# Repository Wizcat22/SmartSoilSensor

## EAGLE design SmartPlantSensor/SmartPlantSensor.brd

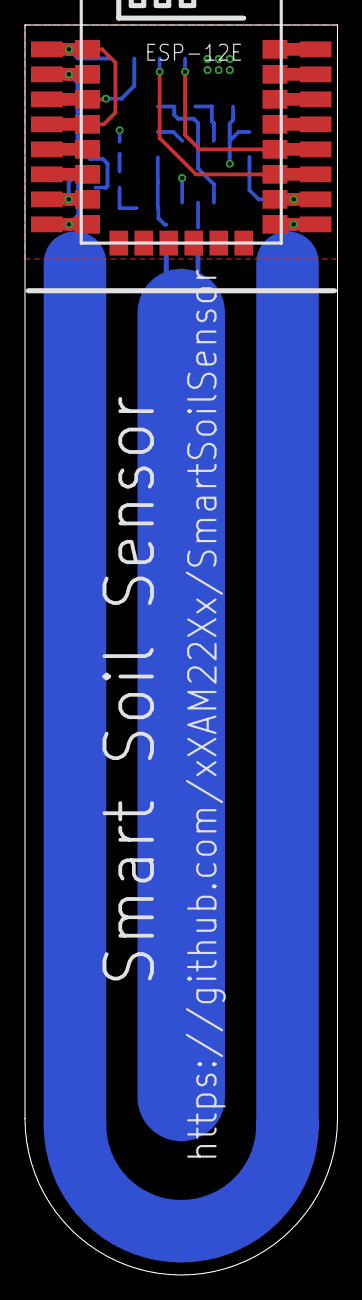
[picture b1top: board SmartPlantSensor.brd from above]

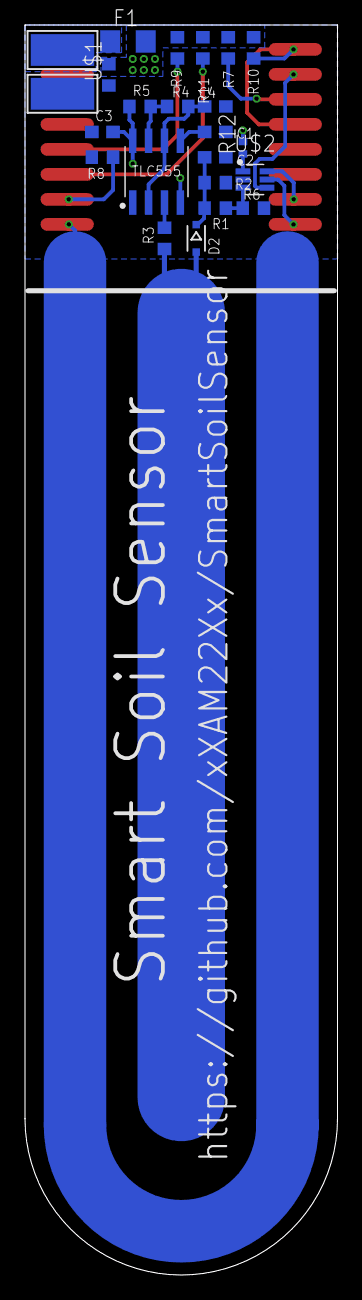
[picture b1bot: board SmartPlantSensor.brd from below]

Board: 2 copper layers, 25.0 x 100.0 mm, 40 parts (23 on the bottom side), 24 nets.

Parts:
C1: 10nF; C0603
C2: 1uF; C0603
C3: 100nF; C0603
C4: 470pF; C0603
D2: 1N4148WS; SOD323-R
ESP-12E: ESP-12E
F1: FUSE; R1206
PAD1, PAD3: WIREPADSMD5-2,5; 5-2,5
PAD5, PAD6, PAD7, PAD8, PAD9, PAD10, PAD11, PAD12, PAD13, PAD14, PAD15, PAD16, PAD17, PAD18, PAD19, PAD20: SMD1,27-2,54
R1: 220k; R0603
R2: 1M; R0603
R3, R7, R8, R9, R10, R11: 10k; R0603
R4: 1k6; R0603
R5: 330; R0603
R6: 100k; R0603
R12: 0; R0402
TLC555: TLC555CD; SOIC8
U$1: TVS_BI_DIODE; R0603
U$2: PI5A3157; SOT65P210X110-6

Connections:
+3V3: C3.2, ESP-12E.8, F1.2, PAD12.1, R5.1, R7.2, R9.2, R10.2, R11.2, R12.2, TLC555.4, TLC555.8, U$1.2, U$2.5
ADC: ESP-12E.2, PAD6.1, U$2.4
DISCH: R4.1, R5.2, TLC555.7
EN: ESP-12E.3, PAD7.1, R7.1
GND: C1.1, C2.2, C3.1, C4.1, ESP-12E.15, PAD3.1, PAD20.1, R2.1, R6.1, R8.1, TLC555.1, U$1.1, U$2.2
IO0: ESP-12E.18, PAD17.1, R9.1
IO2: ESP-12E.17, PAD18.1, R11.1
IO4: ESP-12E.19, PAD16.1
IO5: ESP-12E.20, PAD15.1
IO12: ESP-12E.6, PAD10.1
IO13: ESP-12E.7, PAD11.1, U$2.6
IO14: ESP-12E.5, PAD9.1
IO15: ESP-12E.16, PAD19.1, R8.2
unnamed: C1.2, TLC555.5
unnamed: R12.1, U$2.1
OUT: R3.1, TLC555.3
RST: ESP-12E.1, ESP-12E.4, PAD5.1, PAD8.1, R10.1
RXD: ESP-12E.21, PAD14.1
SADC: R1.1, R6.2, U$2.3
SENSOR: D2.A, R3.2
SENSOR_OUT: C2.1, D2.C, R1.2, R2.2
T: C4.2, R4.2, TLC555.2, TLC555.6
TXD: ESP-12E.22, PAD13.1
VCC: F1.1, PAD1.1

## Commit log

2018-08-21 Create LICENSE
2018-08-27 Initial upload
2018-11-23 Release v1.0.0
2019-07-31 Reworked Layout, added Protection
2019-07-31 Rename
2020-07-17 Added reverse polarity protection
2020-07-24 V1.2
